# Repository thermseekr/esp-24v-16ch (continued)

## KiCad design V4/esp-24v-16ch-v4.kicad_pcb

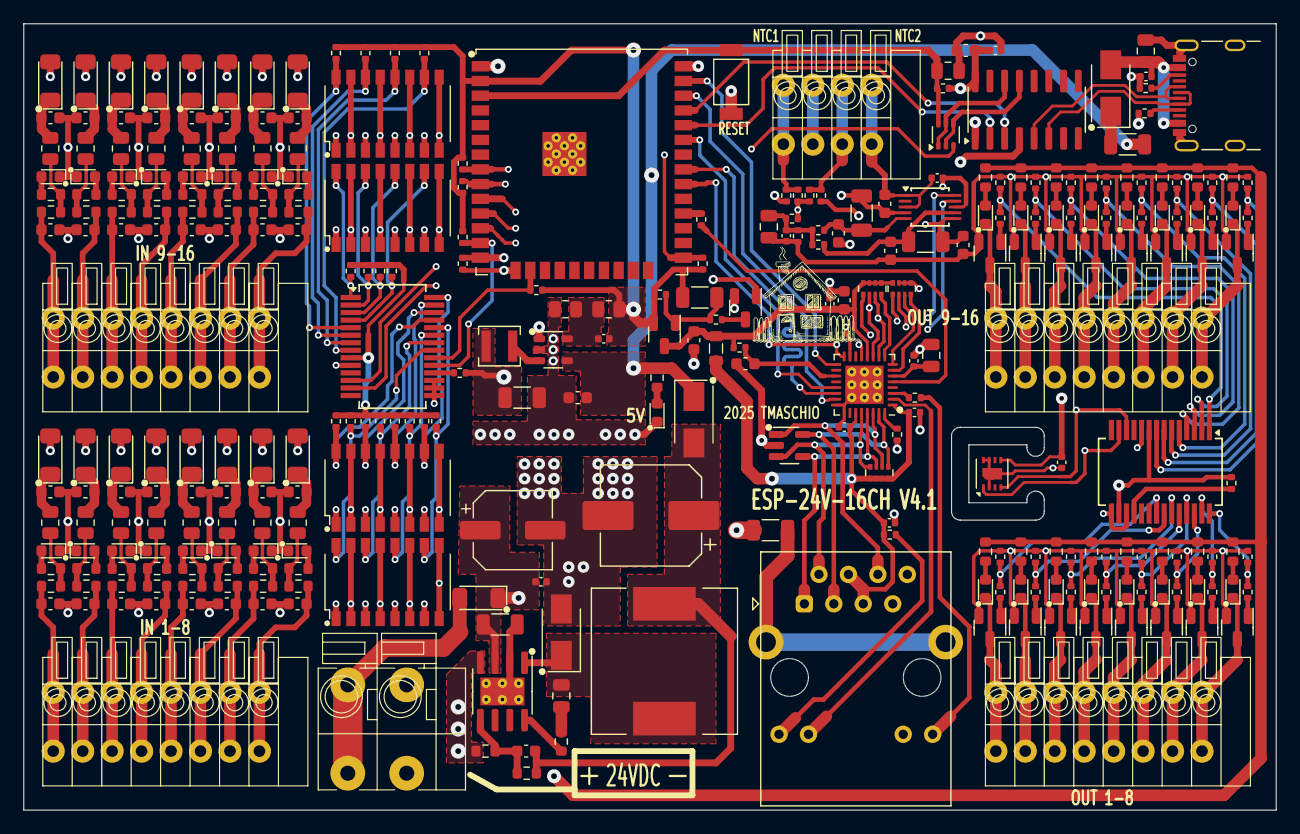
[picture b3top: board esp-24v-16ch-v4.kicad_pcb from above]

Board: 4 copper layers, 108.0 x 67.8 mm, 314 parts (0 on the bottom side), 230 nets.

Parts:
C1, C11, C13, C18, C19: 10uF/10V; C_0603_1608Metric
C2: 47uF/35V; CP_Elec_6.3x5.4
C3, C6, C14, C17, C20, C21, C22, C25, C26, C60: 100nF/50V; C_0402_1005Metric
C4: 22pF/50V; C_0402_1005Metric
C5, C15, C23, C59: 1uF/50V; C_0805_2012Metric
C7, C8: 22uF/10V; C_1206_3216Metric
C9: 100nF/100V; C_0805_2012Metric
C10: 12pF/50V; C_0603_1608Metric
C12: 470uF/16V; CP_Elec_8x10.5
C16: 1nF/2kV; C_1206_3216Metric
C24: 470pF/50V; C_0402_1005Metric
C27, C29, C31, C33, C35, C37, C39, C41, C43, C45, C47, C49, C51, C53, C55, C57: 1nF/50V; C_0603_1608Metric
C28, C30, C32, C34, C36, C38, C40, C42, C44, C46, C48, C50, C52, C54, C56, C58: 33nF/50V; C_0603_1608Metric
C61, C64: 4.7uF/50V; C_1206_3216Metric
C62, C63, C65, C66: 470nF/25V; C_0603_1608Metric
D1, D7, D9, D12, D15, D18, D21, D24, D27, D30, D33, D36, D39, D42, D45, D48, D51, D54, D56, D57, D58, D59, D60, D61, D62, D63, D64, D65, D66, D67, D68, D69, D70: WHITE/0603; LED_0603_1608Metric
D2: SM4007PL; D_SOD-123
D3, D5: SS34; D_SMA
D4: SS510; D_SMA
D6: ESDS314DBV; SOT-23-5
D10, D13, D16, D19, D22, D25, D28, D31, D34, D37, D40, D43, D46, D49, D52, D55: 9V1/500mW; D_SOD-123
F1: 33V/500mA; R_1206_3216Metric
FB1, FB2, FB3, FB4, FB5, FB6, FB7, FB8, FB9, FB10, FB11, FB12, FB13, FB14, FB15, FB16: 600R/100MHz; R_0603_1608Metric
J1, J2, J3, J4: DB141V-2.54-8P; TerminalBlock_Dibo_DB141V-2.54-8P_1x08_P2.54mm_Vertical
J5: VIN; TerminalBlock_Dibo_DB142V-5.08-2P_1x02_P5.08mm_Vertical
J6: USB_C_Receptacle_USB2.0; USB_C_Receptacle_GCT_USB4105-xx-A_16P_TopMnt_Horizontal
J7: ETHERNET; RJ45_HanRun_HR911105A
J8: NTC; TerminalBlock_Dibo_DB141V-2.54-4P_1x04_P2.54mm_Vertical
L1: 2,2uH 1,5A; L_3x3mm_h1.5mm
L2: 33uH 2,1A; L_12x12mm_h6mm
L3: 2A 600R; L_0805_2012Metric
Q1: WPM2015-3/TR; SOT-23
Q2: MMUN2211LT3G; SOT-23
Q3: UMH3N; SOT-363_SC-70-6
Q4, Q5, Q6, Q7, Q8, Q9, Q10, Q11, Q12, Q13, Q14, Q15, Q16, Q17, Q18, Q19: MMBT2222A; SOT-23-Narrow
R1: 560R/100mW; R_0603_1608Metric
R2, R3: 5,1k/62,5mW; R_0402_1005Metric
R4: 100k/125mW; R_0805_2012Metric
R5: 22,1k/125mW; R_0805_2012Metric
R6: 30mR/333mW; R_1206_3216Metric
R7: 5,1R/100mW; R_0603_1608Metric
R8, R12, R14, R19, R22, R26, R77, R80, R83, R86, R89, R92, R95, R98, R101, R104, R107, R110, R113, R116, R119, R122, R123, R124, R125: 10k/62,5mW; R_0402_1005Metric
R9, R24, R25, R27, R78, R81, R84, R87, R90, R93, R96, R99, R102, R105, R108, R111, R114, R117, R120: 1k/62,5mW; R_0402_1005Metric
R10: 300k/100mW; R_0603_1608Metric
R11: 52,3k/100mW; R_0603_1608Metric
R13: 22R/62,5mW; R_0402_1005Metric
R15, R16, R17, R18, R31, R34, R37, R40, R43, R46, R49, R52, R55, R58, R61, R64, R67, R70, R73, R76: 2k2/62,5mW; R_0402_1005Metric
R20, R21: 330R/62,5mW; R_0402_1005Metric
R23: 12,1k/62,5mW; R_0402_1005Metric
R28, R29, R32, R35, R38, R41, R44, R47, R50, R53, R56, R59, R62, R65, R68, R71, R74, R79, R82, R85, R88, R91, R94, R97, R100, R103, R106, R109, R112, R115, R118, R121: 6,8k/100mW; R_0603_1608Metric
R30, R33, R36, R39, R42, R45, R48, R51, R54, R57, R60, R63, R66, R69, R72, R75: 1k8/125mW; R_0805_2012Metric
R128, R129, R130, R131: 680R/62,5mW; R_0402_1005Metric
RN1, RN2: 4x2,2k/62,5mW; R_Array_Convex_4x0402
RN3: 4x49,9R/62,5mW; R_Array_Convex_4x0402
Ref**: Val**; Grandmas_small_silk
SW1: RESET; SW_SPST_Xunpu_TS1088AR02016
U1: SY8089A1AAC; SOT-23-5_Shorter_Pins
U2: TX4138; SOIC-8-1EP_3.9x4.9mm_P1.27mm_EP2.41x3.81mm_ThermalVias
U3: CH340C; SOIC-16_3.9x9.9mm_P1.27mm
U4: ESP32-WROOM-32UE-N16; ESP32-WROOM-32U
U5: LAN8710A; QFN-32-1EP_5x5mm_P0.5mm_EP3.3x3.3mm_ThermalVias
U6, U8: MCP23017_SS; SSOP-28_5.3x10.2mm_P0.65mm
U7: ADS1115IDGS; TSSOP-10_3x3mm_P0.5mm
U9: SHT31-DIS; Sensirion_DFN-8-1EP_2.5x2.5mm_P0.5mm_EP1.1x1.7mm
U10, U11, U12, U13: OR-3H7-4; SOP-16_4.4x10.4mm_P1.27mm

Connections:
+3.3V: C4.1, C7.1, C8.1, C13.1, C14.1, C26.1, L1.2, Q1.2 (S), R4.1, R8.1, R12.1, R14.1, R15.1, R16.1, R17.1, R18.1, R24.1, R25.1, R31.1, R34.1, R37.1, R40.1, R43.1, R46.1, R49.1, R52.1, R55.1, R58.1, R61.1, R64.1, R67.1, R70.1, R73.1, R76.1, U3.4 (V3), U3.16 (VCC), U4.2 (VDD), U6.9 (VDD), U8.9 (VDD), U8.16 (A1), U9.5 (VDD)
+3.3VA: C17.1, C21.1, C22.1, J7.4, J7.5, L3.2, R20.1, RN3.5 (R4.2), RN3.6 (R3.2), RN3.7 (R2.2), RN3.8 (R1.2), U5.1 (VDD2A), U5.27 (VDD1A)
+3.3VLAN: C11.1, C18.1, C20.1, L3.1, Q1.3 (D), R22.2, RN1.5 (R4.2), RN1.6 (R3.2), RN1.7 (R2.2), RN1.8 (R1.2), RN2.8 (R1.2), U5.12 (VDDIO)
+5V: C1.1, C25.1, D5.1 (K), F1.1, R1.1, R122.2, R123.2, R124.2, U1.1 (EN), U1.4 (IN), U7.8 (VDD)
+24V: C2.1, C3.1, D2.1 (K), R6.1, R28.1, R79.1, R82.1, R85.1, R88.1, R91.1, R94.1, R97.1, R100.1, R103.1, R106.1, R109.1, R112.1, R115.1, R118.1, R121.1, U2.3 (VIN)
/I2C Devices/AIN0N: C61.2, C63.1, R129.1, U7.5 (AIN1)
/I2C Devices/AIN0P: C61.1, C62.1, R128.1, U7.4 (AIN0)
/I2C Devices/AIN2N: C64.2, C66.1, R131.1, U7.7 (AIN3)
/I2C Devices/AIN2P: C64.1, C65.1, R130.1, U7.6 (AIN2)
/I2C Devices/MCP1-INTA: R16.2, U4.16 (IO13), U6.20 (INTA)
/I2C Devices/MCP1-INTB: R18.2, U4.13 (IO14), U6.19 (INTB)
/I2C Devices/NTC1: J8.1, R122.1, R128.2
/I2C Devices/NTC2: J8.3, R123.1, R130.2
/I2C Devices/VREF: C59.1, C60.1, R124.1, R125.2, R129.2, R131.2
/I2C Devices//MCP_IN_RST: R24.2, U6.18 (~RESET)
/I2C Devices//MCP_OUT_RST: R25.2, U8.18 (~RESET)
/IN1: C27.1, FB1.1, J1.1
/IN2: C29.1, FB2.1, J1.2
/IN3: C31.1, FB3.1, J1.3
/IN4: C33.1, FB4.1, J1.4
/IN5: C35.1, FB5.1, J1.5
/IN6: C37.1, FB6.1, J1.6
/IN7: C39.1, FB7.1, J1.7
/IN8: C41.1, FB8.1, J1.8
/IN9: C43.1, FB9.1, J2.1
/IN10: C45.1, FB10.1, J2.2
/IN11: C47.1, FB11.1, J2.3
/IN12: C49.1, FB12.1, J2.4
/IN13: C51.1, FB13.1, J2.5
/IN14: C53.1, FB14.1, J2.6
/IN15: C55.1, FB15.1, J2.7
/IN16: C57.1, FB16.1, J2.8
/INPUT1: R31.2, U6.21 (GPA0), U10.16
/INPUT2: R34.2, U6.22 (GPA1), U10.14
/INPUT3: R37.2, U6.23 (GPA2), U10.12
/INPUT4: R40.2, U6.24 (GPA3), U10.10
/INPUT5: R43.2, U6.25 (GPA4), U11.16
/INPUT6: R46.2, U6.26 (GPA5), U11.14
/INPUT7: R49.2, U6.27 (GPA6), U11.12
/INPUT8: R52.2, U6.28 (GPA7), U11.10
/INPUT9: R55.2, U6.1 (GPB0), U12.16
/INPUT10: R58.2, U6.2 (GPB1), U12.14
/INPUT11: R61.2, U6.3 (GPB2), U12.12
/INPUT12: R64.2, U6.4 (GPB3), U12.10
/INPUT13: R67.2, U6.5 (GPB4), U13.16
/INPUT14: R70.2, U6.6 (GPB5), U13.14
/INPUT15: R73.2, U6.7 (GPB6), U13.12
/INPUT16: R76.2, U6.8 (GPB7), U13.10
/LAN/EMAC_CLK: R13.2, U5.5 (XTAL1/CLKIN)
/LAN/EMAC_MDC: U4.37 (IO23), U5.17 (MDC)
/LAN/EMAC_MDIO: RN1.1 (R1.1), U4.30 (IO18), U5.16 (MDIO)
/LAN/EMAC_RX: RN2.1 (R1.1), U4.12 (IO27), U5.15 (COL/CRS_DV/~MODE2)
/LAN/EMAC_RXD0: RN1.2 (R2.1), U4.10 (IO25), U5.11 (RXD0/~MODE0)
/LAN/EMAC_RXD1: RN1.3 (R3.1), U4.11 (IO26), U5.10 (RXD1/~MODE1)
/LAN/EMAC_TXD0: U4.31 (IO19), U5.22 (TXD0)
/LAN/EMAC_TXD1: U4.36 (IO22), U5.23 (TXD1)
/LAN/EMAC_TXEN: U4.33 (IO21), U5.21 (TXEN)
/LAN/LED_G_K: J7.10, U5.2 (LED2/~INTSEL)
/LAN/LED_Y_A: R21.1, U5.3 (LED1/~REGOFF)
/LAN/RD+: D6.5 (I/04), J7.3 (RD+), RN3.1 (R1.1), U5.31 (RXP)
/LAN/RD-: D6.1 (I/01), J7.6 (RD-), RN3.2 (R2.1), U5.30 (RXN)
/LAN/TD+: D6.4 (I/03), J7.1 (TD+), RN3.3 (R3.1), U5.29 (TXP)
/LAN/TD-: D6.3 (I/02), J7.2 (TD-), RN3.4 (R4.1), U5.28 (TXN)
/LAN//PHY_RST: C19.1, R22.1, U5.19 (~RST)
/MCU/ESP_EN: C15.1, Q3.6 (C1), R12.2, SW1.2, U4.3 (EN)
/MCU/I2C_SCL: R15.2, U4.8 (IO32), U6.12 (SCK), U7.10 (SCL), U8.12 (SCK), U9.4 (SCL)
/MCU/I2C_SDA: R17.2, U4.9 (IO33), U6.13 (SDA), U7.9 (SDA), U8.13 (SDA), U9.1 (SDA)
/MCU/PHY_PWR: Q2.1 (B), R19.1, U4.14 (IO12)
/MCU/PROG: Q3.3 (C2), R14.2, U4.25 (IO0)
/MCU/RXD: U3.3 (RXD), U4.35 (TXD0/IO1)
/MCU/TXD: U3.2 (TXD), U4.34 (RXD0/IO3)
/MCU/USB_D+: J6.A6 (D+), J6.B6 (D+), U3.5 (UD+)
/MCU/USB_D-: J6.A7 (D-), J6.B7 (D-), U3.6 (UD-)
/MCU//DTR: Q3.2 (B1), Q3.4 (E2), U3.13 (~DTR)
/MCU//RTS: Q3.1 (E1), Q3.5 (B2), U3.14 (~RTS)
/OUT1: D7.1 (K), J3.1, Q4.3 (C)
/OUT2: D56.1 (K), J3.2, Q5.3 (C)
/OUT3: D57.1 (K), J3.3, Q6.3 (C)
/OUT4: D58.1 (K), J3.4, Q7.3 (C)
/OUT5: D59.1 (K), J3.5, Q8.3 (C)
/OUT6: D60.1 (K), J3.6, Q9.3 (C)
/OUT7: D61.1 (K), J3.7, Q10.3 (C)
/OUT8: D62.1 (K), J3.8, Q11.3 (C)
/OUT9: D63.1 (K), J4.1, Q12.3 (C)
/OUT10: D64.1 (K), J4.2, Q13.3 (C)
/OUT11: D65.1 (K), J4.3, Q14.3 (C)
/OUT12: D66.1 (K), J4.4, Q15.3 (C)
/OUT13: D67.1 (K), J4.5, Q16.3 (C)
/OUT14: D68.1 (K), J4.6, Q17.3 (C)
/OUT15: D69.1 (K), J4.7, Q18.3 (C)
/OUT16: D70.1 (K), J4.8, Q19.3 (C)
/OUTPUT1: R26.2, R27.2, U8.21 (GPA0)
/OUTPUT2: R77.2, R78.2, U8.22 (GPA1)
/OUTPUT3: R80.2, R81.2, U8.23 (GPA2)
/OUTPUT4: R83.2, R84.2, U8.24 (GPA3)
/OUTPUT5: R86.2, R87.2, U8.25 (GPA4)
/OUTPUT6: R89.2, R90.2, U8.26 (GPA5)
/OUTPUT7: R92.2, R93.2, U8.27 (GPA6)
/OUTPUT8: R95.2, R96.2, U8.28 (GPA7)
/OUTPUT9: R98.2, R99.2, U8.1 (GPB0)
/OUTPUT10: R101.2, R102.2, U8.2 (GPB1)
/OUTPUT11: R104.2, R105.2, U8.3 (GPB2)
/OUTPUT12: R107.2, R108.2, U8.4 (GPB3)
/OUTPUT13: R110.2, R111.2, U8.5 (GPB4)
/OUTPUT14: R113.2, R114.2, U8.6 (GPB5)
/OUTPUT15: R116.2, R117.2, U8.7 (GPB6)
/OUTPUT16: R119.2, R120.2, U8.8 (GPB7)
/Power/3.3V_REF: C4.2, R4.2, R5.1, U1.5 (FB)
/Power/5V_MAIN: C10.1, C12.1, D5.2 (A), L2.2, R10.1
/Power/5V_USB: C5.1, C6.1, D3.2 (A), J6.A4 (VBUS), J6.A9 (VBUS), J6.B4 (VBUS), J6.B9 (VBUS)
/Power/24VIN: D2.2 (A), J5.1
/Power/USB_A5: J6.A5 (CC1), R2.1
/Power/USB_B5: J6.B5 (CC2), R3.1
GND: C1.2, C2.2, C3.2, C5.2, C6.2, C7.2, C11.2, C12.2, C13.2, C14.2, C15.2, C16.2, C17.2, C18.2, C19.2, C20.2, C21.2, C22.2, C23.2, C24.2, C25.2, C26.2, C27.2, C28.2, C29.2, C30.2, C31.2, C32.2, C33.2, C34.2, C35.2, C36.2, C37.2, C38.2, C39.2, C40.2, C41.2, C42.2, C43.2, C44.2, C45.2, C46.2, C47.2, C48.2, C49.2, C50.2, C51.2, C52.2, C53.2, C54.2, C55.2, C56.2, C57.2, C58.2, C59.2, C60.2, C62.2, C63.2, C65.2, C66.2, D1.1 (K), D4.2 (A), D6.2 (GND), D9.1 (K), D12.1 (K), D15.1 (K), D18.1 (K), D21.1 (K), D24.1 (K), D27.1 (K), D30.1 (K), D33.1 (K), D36.1 (K), D39.1 (K), D42.1 (K), D45.1 (K), D48.1 (K), D51.1 (K), D54.1 (K), J5.2, J6.A1 (GND), J6.A12 (GND), J6.B1 (GND), J6.B12 (GND), J6.S1 (SHIELD), J7.8, J7.11, J8.2, J8.4, Q2.2 (E), Q4.2 (E), Q5.2 (E), Q6.2 (E), Q7.2 (E), Q8.2 (E), Q9.2 (E), Q10.2 (E), Q11.2 (E), Q12.2 (E), Q13.2 (E), Q14.2 (E), Q15.2 (E), Q16.2 (E), Q17.2 (E), Q18.2 (E), Q19.2 (E), R2.2, R3.2, R5.2, R11.2, R19.2, R23.2, R26.1, R77.1, R80.1, R83.1, R86.1, R89.1, R92.1, R95.1, R98.1, R101.1, R104.1, R107.1, R110.1, R113.1, R116.1, R119.1, R125.1, RN2.5 (R4.2), RN2.6 (R3.2), RN2.7 (R2.2), SW1.1, U1.2 (GND), U2.4 (GND), U3.1 (GND), U4.1 (GND), U4.15 (GND), U4.38 (GND), U4.39 (GND), U5.24 (TXD2), U5.25 (TXD3), U5.33 (VSS), U6.10 (VSS), U6.15 (A0), U6.16 (A1), U6.17 (A2), U7.1 (ADDR), U7.3 (GND), U8.10 (VSS), U8.15 (A0), U8.17 (A2), U9.2 (ADDR), U9.7 (R), U9.8 (VSS), U9.9 (VSS), U10.2, U10.4, U10.6, U10.8, U10.9, U10.11, U10.13, U10.15, U11.2, U11.4, U11.6, U11.8, U11.9, U11.11, U11.13, U11.15, U12.2, U12.4, U12.6, U12.8, U12.9, U12.11, U12.13, U12.15, U13.2, U13.4, U13.6, U13.8, U13.9, U13.11, U13.13, U13.15
unnamed: C9.1, R7.1
unnamed: C16.1, J7.SH
unnamed: D1.2 (A), R1.2
unnamed: D3.1 (K), F1.2
unnamed: C9.2, D4.1 (K), L2.1, U2.1 (SW)
unnamed: D7.2 (A), R28.2
unnamed: D9.2 (A), R29.2
unnamed: D10.2 (A), U10.1
unnamed: C28.1, D10.1 (K), R30.1
unnamed: D12.2 (A), R32.2
unnamed: D13.2 (A), U10.3
unnamed: C30.1, D13.1 (K), R33.1
unnamed: D15.2 (A), R35.2
unnamed: D16.2 (A), U10.5
unnamed: C32.1, D16.1 (K), R36.1
unnamed: D18.2 (A), R38.2
unnamed: D19.2 (A), U10.7
unnamed: C34.1, D19.1 (K), R39.1
unnamed: D21.2 (A), R41.2
unnamed: D22.2 (A), U11.1
unnamed: C36.1, D22.1 (K), R42.1
unnamed: D24.2 (A), R44.2
unnamed: D25.2 (A), U11.3
unnamed: C38.1, D25.1 (K), R45.1
unnamed: D27.2 (A), R47.2
unnamed: D28.2 (A), U11.5
unnamed: C40.1, D28.1 (K), R48.1
unnamed: D30.2 (A), R50.2
unnamed: D31.2 (A), U11.7
unnamed: C42.1, D31.1 (K), R51.1
unnamed: D33.2 (A), R53.2
unnamed: D34.2 (A), U12.1
unnamed: C44.1, D34.1 (K), R54.1
unnamed: D36.2 (A), R56.2
unnamed: D37.2 (A), U12.3
unnamed: C46.1, D37.1 (K), R57.1
unnamed: D39.2 (A), R59.2
unnamed: D40.2 (A), U12.5
unnamed: C48.1, D40.1 (K), R60.1
unnamed: D42.2 (A), R62.2
unnamed: D43.2 (A), U12.7
unnamed: C50.1, D43.1 (K), R63.1
unnamed: D45.2 (A), R65.2
unnamed: D46.2 (A), U13.1
unnamed: C52.1, D46.1 (K), R66.1
unnamed: D48.2 (A), R68.2
unnamed: D49.2 (A), U13.3
unnamed: C54.1, D49.1 (K), R69.1
unnamed: D51.2 (A), R71.2
unnamed: D52.2 (A), U13.5
unnamed: C56.1, D52.1 (K), R72.1
unnamed: D54.2 (A), R74.2
unnamed: D55.2 (A), U13.7
unnamed: C58.1, D55.1 (K), R75.1
unnamed: D56.2 (A), R79.2
unnamed: D57.2 (A), R82.2
unnamed: D58.2 (A), R85.2
unnamed: D59.2 (A), R88.2
unnamed: D60.2 (A), R91.2
unnamed: D61.2 (A), R94.2
unnamed: D62.2 (A), R97.2
unnamed: D63.2 (A), R100.2
unnamed: D64.2 (A), R103.2
unnamed: D65.2 (A), R106.2
unnamed: D66.2 (A), R109.2
unnamed: D67.2 (A), R112.2
unnamed: D68.2 (A), R115.2
unnamed: D69.2 (A), R118.2
unnamed: D70.2 (A), R121.2
unnamed: FB1.2, R29.1, R30.2
unnamed: FB2.2, R32.1, R33.2
unnamed: FB3.2, R35.1, R36.2
unnamed: FB4.2, R38.1, R39.2
unnamed: FB5.2, R41.1, R42.2
unnamed: FB6.2, R44.1, R45.2
unnamed: FB7.2, R47.1, R48.2
unnamed: FB8.2, R50.1, R51.2
unnamed: FB9.2, R53.1, R54.2
unnamed: FB10.2, R56.1, R57.2
unnamed: FB11.2, R59.1, R60.2
unnamed: FB12.2, R62.1, R63.2
unnamed: FB13.2, R65.1, R66.2
unnamed: FB14.2, R68.1, R69.2
unnamed: FB15.2, R71.1, R72.2
unnamed: FB16.2, R74.1, R75.2
unnamed: J7.9, R20.2
unnamed: J7.12, R21.2
unnamed: C8.2, Q1.1 (G), R8.2, R9.2
unnamed: Q2.3 (C), R9.1
unnamed: Q4.1 (B), R27.1
unnamed: Q5.1 (B), R78.1
unnamed: Q6.1 (B), R81.1
unnamed: Q7.1 (B), R84.1
unnamed: Q8.1 (B), R87.1
unnamed: Q9.1 (B), R90.1
unnamed: Q10.1 (B), R93.1
unnamed: Q11.1 (B), R96.1
unnamed: Q12.1 (B), R99.1
unnamed: Q13.1 (B), R102.1
unnamed: Q14.1 (B), R105.1
unnamed: Q15.1 (B), R108.1
unnamed: Q16.1 (B), R111.1
unnamed: Q17.1 (B), R114.1
unnamed: Q18.1 (B), R117.1
unnamed: Q19.1 (B), R120.1
unnamed: R6.2, U2.2 (ILIM), U2.9 (ILIM)
unnamed: RN1.4 (R4.1), U5.9 (RXD2/~RMIISEL)
unnamed: RN2.2 (R2.1), U5.13 (RXER/RXD4/~PHYAD0)
unnamed: RN2.3 (R3.1), U5.8 (RXD3/~PHYAD2)
unnamed: RN2.4 (R4.1), U5.7 (RXCLK/~PHYAD1)
unnamed: L1.1, U1.3 (LX)
unnamed: R7.2, U2.8 (BS)
unnamed: C10.2, R10.2, R11.1, U2.5 (FB)
unnamed: R13.1, U4.28 (IO17)
unnamed: R23.1, U5.32 (RBIAS)
unnamed: C23.1, C24.1, U5.6 (VDDCR)

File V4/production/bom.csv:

Designator,Footprint,Quantity,Value,LCSC Part #
"C1, C11, C13, C18, C19",0603,5,10uF/10V,C19702
C10,0603,1,12pF/50V,C38523
C12,CP_Elec_8x10.5,1,470uF/16V,C96179
"C14, C17, C20, C21, C22, C25, C3, C6, C60",0402,9,100nF/50V,C307331
"C15, C23, C5, C59",0805,4,1uF/50V,C28323
C16,1206,1,1nF/2kV,C161353
C2,CP_Elec_6.3x5.4,1,47uF/35V,C129415
C24,0402,1,470pF/50V,C1537
"C27, C29, C31, C33, C35, C37, C39, C41",0603,8,1nF/50V,C1588
"C28, C30, C32, C34, C36, C38, C40, C42",0603,8,33nF/50V,C21117
C4,0402,1,22pF/50V,C1555
"C61, C64",1206,2,4.7uF/50V,C29823
"C62, C63, C65, C66",0603,4,470nF/25V,C1623
"C7, C8",1206,2,22uF/10V,C5672
C9,0805,1,100nF/100V,C28233
"D1, D12, D15, D18, D21, D24, D27, D30, D56, D57, D58, D59, D60, D61, D62, D7, D9",0603,17,WHITE/0603,C2290
"D10, D13, D16, D19, D22, D25, D28, D31",D_SOD-123,8,9V1/500mW,C19077407
D2,D_SOD-123,1,SM4007PL,C64898
"D3, D5",D_SMA,2,SS34,C8678
D4,D_SMA,1,SS510,C65010
D6,SOT-23-5,1,ESDS314DBV,C1847859
F1,1206,1,33V/500mA,C70077
"FB1, FB2, FB3, FB4, FB5, FB6, FB7, FB8",0603,8,600R/100MHz,C85833
"J1, J3",TerminalBlock_Dibo_DB141V-2.54-8P_1x08_P2.54mm_Vertical,2,DB141V-2.54-8P,C2898750
J5,TerminalBlock_Dibo_DB142V-5.08-2P_1x02_P5.08mm_Vertical,1,VIN,C2898699
J6,USB_C_Receptacle_GCT_USB4105-xx-A_16P_TopMnt_Horizontal,1,USB_C_Receptacle_USB2.0,C2765186
J7,RJ45_HanRun_HR911105A,1,ETHERNET,C12074
J8,TerminalBlock_Dibo_DB141V-2.54-4P_1x04_P2.54mm_Vertical,1,NTC,C2898746
L1,L_3x3mm_h1.5mm,1,"2,2uH 1,5A",C370424
L2,L_12x12mm_h6mm,1,"33uH 2,1A",C169386
L3,0805,1,2A 600R,C139168
Q1,SOT-23,1,WPM2015-3/TR,C558305
"Q10, Q11, Q4, Q5, Q6, Q7, Q8, Q9",SOT-23-Narrow,8,MMBT2222A,C8512
Q2,SOT-23,1,MMUN2211LT3G,C150229
Q3,SOT-363_SC-70-6,1,UMH3N,C62892
R1,0603,1,560R/100mW,C23204
R10,0603,1,300k/100mW,C23024
R11,0603,1,"52,3k/100mW",C185323
"R12, R122, R123, R124, R125, R14, R19, R22, R26, R77, R8, R80, R83, R86, R89, R92, R95",0402,17,"10k/62,5mW",C25744
"R128, R129, R130, R131",0402,4,"680R/62,5mW",C25130
R13,0402,1,"22R/62,5mW",C25092
"R15, R16, R17, R18, R31, R34, R37, R40, R43, R46, R49, R52",0402,12,"2k2/62,5mW",C25879
"R2, R3",0402,2,"5,1k/62,5mW",C105872
"R20, R21",0402,2,"330R/62,5mW",C25104
R23,0402,1,"12,1k/62,5mW",C25852
"R24, R25, R27, R78, R81, R84, R87, R9, R90, R93, R96",0402,11,"1k/62,5mW",C11702
"R28, R29, R32, R35, R38, R41, R44, R47, R50, R79, R82, R85, R88, R91, R94, R97",0603,16,"6,8k/100mW",C23212
"R30, R33, R36, R39, R42, R45, R48, R51",0805,8,1k8/125mW,C17398
R4,0805,1,100k/125mW,C149504
R5,0805,1,"22,1k/125mW",C17552
R6,1206,1,30mR/333mW,C473665
R7,0603,1,"5,1R/100mW",C25197
"RN1, RN2",R_Array_Convex_4x0402,2,"4x2,2k/62,5mW",C728724
RN3,R_Array_Convex_4x0402,1,"4x49,9R/62,5mW",C136850
SW1,SW_SPST_Xunpu_TS1088AR02016,1,RESET,C720477
U1,SOT-23-5_Shorter_Pins,1,SY8089A1AAC,C479074
"U10, U11",SOP-16_4.4x10.4mm_P1.27mm,2,OR-3H7-4,C2838427
U2,SOIC-8-1EP_3.9x4.9mm_P1.27mm_EP2.41x3.81mm_ThermalVias,1,TX4138,C329267
U3,SOIC-16_3.9x9.9mm_P1.27mm,1,CH340C,C84681
U4,ESP32-WROOM-32U,1,ESP32-WROOM-32UE-N16,C701346
U5,QFN-32-1EP_5x5mm_P0.5mm_EP3.3x3.3mm_ThermalVias,1,LAN8710A,C46185
"U6, U8",SSOP-28_5.3x10.2mm_P0.65mm,2,MCP23017_SS,C558584
U7,TSSOP-10_3x3mm_P0.5mm,1,ADS1115IDGS,C37593

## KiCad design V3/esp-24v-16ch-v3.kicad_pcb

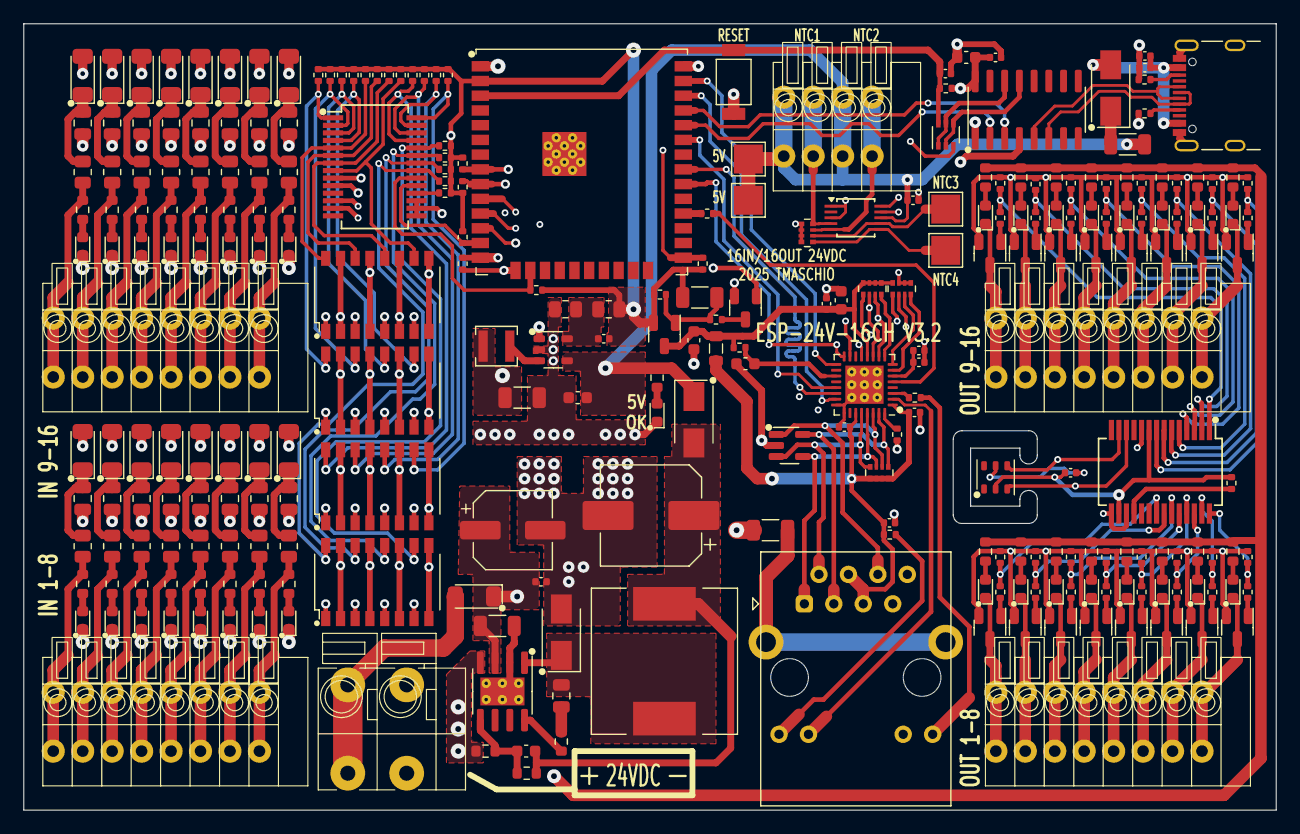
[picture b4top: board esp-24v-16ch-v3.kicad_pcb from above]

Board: 4 copper layers, 108.0 x 67.8 mm, 270 parts (0 on the bottom side), 211 nets.

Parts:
C1, C9, C11, C16, C17: 10uF/10V; C_0603_1608Metric
C2: 47uF/35V; CP_Elec_6.3x5.4
C3: 22pF/50V; C_0402_1005Metric
C4, C12, C15, C18, C19, C20, C40, C41, C42: 100nF/50V; C_0402_1005Metric
C5, C6: 22uF/10V; C_1206_3216Metric
C7: 100nF/100V; C_0805_2012Metric
C8: 12pF/50V; C_0603_1608Metric
C10: 470uF/16V; CP_Elec_8x10.5
C13, C21, C39: 1uF/25V; C_0402_1005Metric
C14: 1nF/2kV; C_1206_3216Metric
C22: 470pF/50V; C_0402_1005Metric
C23, C24, C25, C26, C27, C28, C29, C30, C31, C32, C33, C34, C35, C36, C37, C38: 33nF/50V; C_0805_2012Metric
D1: SM4007PL; D_SOD-123
D2, D7, D8, D9, D10, D15, D16, D17, D18, D23, D24, D25, D26, D31, D32, D33, D34, D39, D40, D41, D42, D43, D44, D45, D46, D47, D48, D49, D50, D51, D52, D53, D54: EMERALD/0603; LED_0603_1608Metric
D3, D5: SS34; D_SMA
D4: SS510; D_SMA
D6: ESDS314DBV; SOT-23-5
D11, D12, D13, D14, D19, D20, D21, D22, D27, D28, D29, D30, D35, D36, D37, D38: 9V1/500mW; D_SOD-123
F1: 33V/500mA; R_1206_3216Metric
H1, H2: +5V; TestPoint_Pad_2.5x2.5mm
H3: AIN2; TestPoint_Pad_2.5x2.5mm
H4: AIN3; TestPoint_Pad_2.5x2.5mm
J1: VIN; TerminalBlock_Dibo_DB142V-5.08-2P_1x02_P5.08mm_Vertical
J2: USB_C_Receptacle_USB2.0; USB_C_Receptacle_GCT_USB4105-xx-A_16P_TopMnt_Horizontal
J3, J4, J5, J6: DB141V-2.54-8P; TerminalBlock_Dibo_DB141V-2.54-8P_1x08_P2.54mm_Vertical
J7: ETHERNET; RJ45_HanRun_HR911105A
J8: NTC; TerminalBlock_Dibo_DB141V-2.54-4P_1x04_P2.54mm_Vertical
L1: 2,2uH 1,5A; L_3x3mm_h1.5mm
L2: 33uH 2,1A; L_12x12mm_h6mm
L3: 2A 600R; L_0805_2012Metric
Q1: WPM2015-3/TR; SOT-23
Q2: MMUN2211LT3G; SOT-23
Q3: UMH3N; SOT-363_SC-70-6
Q4, Q5, Q6, Q7, Q8, Q9, Q10, Q11, Q12, Q13, Q14, Q15, Q16, Q17, Q18, Q19: MMBT2222A; SOT-23-Narrow
R1: 560R/100mW; R_0603_1608Metric
R2: 100k/125mW; R_0805_2012Metric
R3: 22,1k/125mW; R_0805_2012Metric
R4: 30mR/333mW; R_1206_3216Metric
R5: 5,1R/100mW; R_0603_1608Metric
R6, R10, R11, R12, R24, R81, R82, R83, R84, R93, R94, R95, R96, R105, R106, R107, R108, R117, R118, R119, R120: 10k/62,5mW; R_0402_1005Metric
R7, R31, R32, R85, R86, R87, R88, R97, R98, R99, R100, R109, R110, R111, R112, R121, R122, R123, R124: 1k/62,5mW; R_0402_1005Metric
R8: 300k/100mW; R_0603_1608Metric
R9: 52,3k/100mW; R_0603_1608Metric
R13, R14, R41, R42, R43, R44, R53, R54, R55, R56, R65, R66, R67, R68, R77, R78, R79, R80, R129, R130: 2k2/62,5mW; R_0402_1005Metric
R15: 22R/62,5mW; R_0402_1005Metric
R16, R17: 330R/62,5mW; R_0402_1005Metric
R26: 12,1k/62,5mW; R_0402_1005Metric
R33, R34, R35, R36, R45, R46, R47, R48, R57, R58, R59, R60, R69, R70, R71, R72, R89, R90, R91, R92, R101, R102, R103, R104, R113, R114, R115, R116, R125, R126, R127, R128: 6,8k/100mW; R_0603_1608Metric
R37, R38, R39, R40, R49, R50, R51, R52, R61, R62, R63, R64, R73, R74, R75, R76: 1k8/125mW; R_0805_2012Metric
R131, R132: 5,1k/62,5mW; R_0402_1005Metric
RN1: 4x49,9R/62,5mW; R_Array_Convex_4x0402
RN2, RN3: 4x2,2k/62,5mW; R_Array_Convex_4x0402
RN4: 4x3k/62,5mW; R_Array_Convex_4x0402
SW1: RESET; SW_SPST_Xunpu_TS1088AR02016
U1: SY8089A1AAC; SOT-23-5_Shorter_Pins
U2: TX4138; SOIC-8-1EP_3.9x4.9mm_P1.27mm_EP2.41x3.81mm_ThermalVias
U3: CH340C; SOIC-16_3.9x9.9mm_P1.27mm
U4: ESP32-WROOM-32UE-N16; ESP32-WROOM-32U
U5: LAN8710A; QFN-32-1EP_5x5mm_P0.5mm_EP3.3x3.3mm_ThermalVias
U6, U7: MCP23017_SS; SSOP-28_5.3x10.2mm_P0.65mm
U8, U9, U10, U11: OR-3H7-4; SOP-16_4.4x10.4mm_P1.27mm
U12: AHT20; DFN-6-3x3mm_P1mm
U13: ADS1115IDGS; TSSOP-10_3x3mm_P0.5mm

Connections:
+3.3V: C3.1, C5.1, C6.1, C11.1, C12.1, C41.1, L1.2, Q1.2 (S), R2.1, R6.1, R10.1, R11.1, R13.1, R14.1, R31.1, R32.1, R41.1, R42.1, R43.1, R44.1, R53.1, R54.1, R55.1, R56.1, R65.1, R66.1, R67.1, R68.1, R77.1, R78.1, R79.1, R80.1, R129.1, R130.1, U3.4 (V3), U3.16 (VCC), U4.2 (VDD), U6.9 (VDD), U7.9 (VDD), U7.16 (A1), U12.2 (VDD)
+3.3VA: C15.1, C19.1, C20.1, J7.4, J7.5, L3.2, R16.1, RN1.5 (R4.2), RN1.6 (R3.2), RN1.7 (R2.2), RN1.8 (R1.2), U5.1 (VDD2A), U5.27 (VDD1A)
+3.3VLAN: C9.1, C16.1, C18.1, L3.1, Q1.3 (D), R24.2, RN2.5 (R4.2), RN2.6 (R3.2), RN2.7 (R2.2), RN2.8 (R1.2), RN3.8 (R1.2), U5.12 (VDDIO)
+5V: C1.1, C42.1, D5.1 (K), F1.1, H1.1, H2.1, J8.1, J8.3, R1.1, U1.1 (EN), U1.4 (IN), U13.8 (VDD)
+24V: C2.1, C4.1, D1.1 (K), R4.1, R89.1, R90.1, R91.1, R92.1, R101.1, R102.1, R103.1, R104.1, R113.1, R114.1, R115.1, R116.1, R125.1, R126.1, R127.1, R128.1, U2.3 (VIN)
/I2C Devices/IN1: R41.2, U6.21 (GPA0), U8.16
/I2C Devices/IN2: R42.2, U6.22 (GPA1), U8.14
/I2C Devices/IN3: R43.2, U6.23 (GPA2), U8.12
/I2C Devices/IN4: R44.2, U6.24 (GPA3), U8.10
/I2C Devices/IN5: R53.2, U6.25 (GPA4), U9.16
/I2C Devices/IN6: R54.2, U6.26 (GPA5), U9.14
/I2C Devices/IN7: R55.2, U6.27 (GPA6), U9.12
/I2C Devices/IN8: R56.2, U6.28 (GPA7), U9.10
/I2C Devices/IN9: R65.2, U6.1 (GPB0), U10.16
/I2C Devices/IN10: R66.2, U6.2 (GPB1), U10.14
/I2C Devices/IN11: R67.2, U6.3 (GPB2), U10.12
/I2C Devices/IN12: R68.2, U6.4 (GPB3), U10.10
/I2C Devices/IN13: R77.2, U6.5 (GPB4), U11.16
/I2C Devices/IN14: R78.2, U6.6 (GPB5), U11.14
/I2C Devices/IN15: R79.2, U6.7 (GPB6), U11.12
/I2C Devices/IN16: R80.2, U6.8 (GPB7), U11.10
/I2C Devices/MCP1-INTA: R129.2, U4.16 (IO13), U6.20 (INTA)
/I2C Devices/MCP1-INTB: R130.2, U4.13 (IO14), U6.19 (INTB)
/I2C Devices/OUT1: R81.2, R85.2, U7.21 (GPA0)
/I2C Devices/OUT2: R82.2, R86.2, U7.22 (GPA1)
/I2C Devices/OUT3: R83.2, R87.2, U7.23 (GPA2)
/I2C Devices/OUT4: R84.2, R88.2, U7.24 (GPA3)
/I2C Devices/OUT5: R93.2, R97.2, U7.25 (GPA4)
/I2C Devices/OUT6: R94.2, R98.2, U7.26 (GPA5)
/I2C Devices/OUT7: R95.2, R99.2, U7.27 (GPA6)
/I2C Devices/OUT8: R96.2, R100.2, U7.28 (GPA7)
/I2C Devices/OUT9: R105.2, R109.2, U7.1 (GPB0)
/I2C Devices/OUT10: R106.2, R110.2, U7.2 (GPB1)
/I2C Devices/OUT11: R107.2, R111.2, U7.3 (GPB2)
/I2C Devices/OUT12: R108.2, R112.2, U7.4 (GPB3)
/I2C Devices/OUT13: R117.2, R121.2, U7.5 (GPB4)
/I2C Devices/OUT14: R118.2, R122.2, U7.6 (GPB5)
/I2C Devices/OUT15: R119.2, R123.2, U7.7 (GPB6)
/I2C Devices/OUT16: R120.2, R124.2, U7.8 (GPB7)
/Inputs 1-16/J4-IN1: J3.1, R33.1, R37.2
/Inputs 1-16/J4-IN2: J3.2, R34.1, R38.2
/Inputs 1-16/J4-IN3: J3.3, R35.1, R39.2
/Inputs 1-16/J4-IN4: J3.4, R36.1, R40.2
/Inputs 1-16/J4-IN5: J3.5, R45.1, R49.2
/Inputs 1-16/J4-IN6: J3.6, R46.1, R50.2
/Inputs 1-16/J4-IN7: J3.7, R47.1, R51.2
/Inputs 1-16/J4-IN8: J3.8, R48.1, R52.2
/Inputs 1-16/J5-IN9: J4.1, R57.1, R61.2
/Inputs 1-16/J5-IN10: J4.2, R58.1, R62.2
/Inputs 1-16/J5-IN11: J4.3, R59.1, R63.2
/Inputs 1-16/J5-IN12: J4.4, R60.1, R64.2
/Inputs 1-16/J5-IN13: J4.5, R69.1, R73.2
/Inputs 1-16/J5-IN14: J4.6, R70.1, R74.2
/Inputs 1-16/J5-IN15: J4.7, R71.1, R75.2
/Inputs 1-16/J5-IN16: J4.8, R72.1, R76.2
/LAN/EMAC_CLK: R15.2, U5.5 (XTAL1/CLKIN)
/LAN/EMAC_MDC: U4.37 (IO23), U5.17 (MDC)
/LAN/EMAC_MDIO: RN2.1 (R1.1), U4.30 (IO18), U5.16 (MDIO)
/LAN/EMAC_RX: RN3.1 (R1.1), U4.12 (IO27), U5.15 (COL/CRS_DV/~MODE2)
/LAN/EMAC_RXD0: RN2.2 (R2.1), U4.10 (IO25), U5.11 (RXD0/~MODE0)
/LAN/EMAC_RXD1: RN2.3 (R3.1), U4.11 (IO26), U5.10 (RXD1/~MODE1)
/LAN/EMAC_TXD0: U4.31 (IO19), U5.22 (TXD0)
/LAN/EMAC_TXD1: U4.36 (IO22), U5.23 (TXD1)
/LAN/EMAC_TXEN: U4.33 (IO21), U5.21 (TXEN)
/LAN/LED_G_K: J7.10, U5.2 (LED2/~INTSEL)
/LAN/LED_Y_A: R17.1, U5.3 (LED1/~REGOFF)
/LAN/RD+: D6.5 (I/04), J7.3 (RD+), RN1.1 (R1.1), U5.31 (RXP)
/LAN/RD-: D6.1 (I/01), J7.6 (RD-), RN1.2 (R2.1), U5.30 (RXN)
/LAN/TD+: D6.4 (I/03), J7.1 (TD+), RN1.3 (R3.1), U5.29 (TXP)
/LAN/TD-: D6.3 (I/02), J7.2 (TD-), RN1.4 (R4.1), U5.28 (TXN)
/MCU/I2C_SCL: R13.2, U4.8 (IO32), U6.12 (SCK), U7.12 (SCK), U12.3 (SCL), U13.10 (SCL)
/MCU/I2C_SDA: R14.2, U4.9 (IO33), U6.13 (SDA), U7.13 (SDA), U12.4 (SDA), U13.9 (SDA)
/MCU/PHY_PWR: Q2.1 (B), R12.1, U4.14 (IO12)
/MCU/USB_D+: J2.A6 (D+), J2.B6 (D+), U3.5 (UD+)
/MCU/USB_D-: J2.A7 (D-), J2.B7 (D-), U3.6 (UD-)
/Outputs 1-16/J8-OUT1: D39.1 (K), J5.1, Q4.3 (C)
/Outputs 1-16/J8-OUT2: D40.1 (K), J5.2, Q5.3 (C)
/Outputs 1-16/J8-OUT3: D41.1 (K), J5.3, Q6.3 (C)
/Outputs 1-16/J8-OUT4: D42.1 (K), J5.4, Q7.3 (C)
/Outputs 1-16/J8-OUT5: D43.1 (K), J5.5, Q8.3 (C)
/Outputs 1-16/J8-OUT6: D44.1 (K), J5.6, Q9.3 (C)
/Outputs 1-16/J8-OUT7: D45.1 (K), J5.7, Q10.3 (C)
/Outputs 1-16/J8-OUT8: D46.1 (K), J5.8, Q11.3 (C)
/Outputs 1-16/J9-OUT9: D47.1 (K), J6.1, Q12.3 (C)
/Outputs 1-16/J9-OUT10: D48.1 (K), J6.2, Q13.3 (C)
/Outputs 1-16/J9-OUT11: D49.1 (K), J6.3, Q14.3 (C)
/Outputs 1-16/J9-OUT12: D50.1 (K), J6.4, Q15.3 (C)
/Outputs 1-16/J9-OUT13: D51.1 (K), J6.5, Q16.3 (C)
/Outputs 1-16/J9-OUT14: D52.1 (K), J6.6, Q17.3 (C)
/Outputs 1-16/J9-OUT15: D53.1 (K), J6.7, Q18.3 (C)
/Outputs 1-16/J9-OUT16: D54.1 (K), J6.8, Q19.3 (C)
GND: C1.2, C2.2, C4.2, C5.2, C9.2, C10.2, C11.2, C12.2, C13.2, C14.2, C15.2, C16.2, C17.2, C18.2, C19.2, C20.2, C21.2, C22.2, C23.2, C24.2, C25.2, C26.2, C27.2, C28.2, C29.2, C30.2, C31.2, C32.2, C33.2, C34.2, C35.2, C36.2, C37.2, C38.2, C39.2, C40.2, C41.2, C42.2, D2.1 (K), D4.2 (A), D6.2 (GND), D7.1 (K), D8.1 (K), D9.1 (K), D10.1 (K), D15.1 (K), D16.1 (K), D17.1 (K), D18.1 (K), D23.1 (K), D24.1 (K), D25.1 (K), D26.1 (K), D31.1 (K), D32.1 (K), D33.1 (K), D34.1 (K), J1.2, J2.A1 (GND), J2.A12 (GND), J2.B1 (GND), J2.B12 (GND), J2.S1 (SHIELD), J7.8, J7.11, Q2.2 (E), Q4.2 (E), Q5.2 (E), Q6.2 (E), Q7.2 (E), Q8.2 (E), Q9.2 (E), Q10.2 (E), Q11.2 (E), Q12.2 (E), Q13.2 (E), Q14.2 (E), Q15.2 (E), Q16.2 (E), Q17.2 (E), Q18.2 (E), Q19.2 (E), R3.2, R9.2, R12.2, R26.2, R81.1, R82.1, R83.1, R84.1, R93.1, R94.1, R95.1, R96.1, R105.1, R106.1, R107.1, R108.1, R117.1, R118.1, R119.1, R120.1, R131.2, R132.2, RN3.5 (R4.2), RN3.6 (R3.2), RN3.7 (R2.2), RN4.1 (R1.1), RN4.2 (R2.1), RN4.3 (R3.1), RN4.4 (R4.1), SW1.1, U1.2 (GND), U2.4 (GND), U3.1 (GND), U4.1 (GND), U4.15 (GND), U4.38 (GND), U4.39 (GND), U5.24 (TXD2), U5.25 (TXD3), U5.33 (VSS), U6.10 (VSS), U6.15 (A0), U6.16 (A1), U6.17 (A2), U7.10 (VSS), U7.15 (A0), U7.17 (A2), U8.2, U8.4, U8.6, U8.8, U8.9, U8.11, U8.13, U8.15, U9.2, U9.4, U9.6, U9.8, U9.9, U9.11, U9.13, U9.15, U10.2, U10.4, U10.6, U10.8, U10.9, U10.11, U10.13, U10.15, U11.2, U11.4, U11.6, U11.8, U11.9, U11.11, U11.13, U11.15, U12.5 (GND), U13.1 (ADDR), U13.3 (GND)
unnamed: C7.1, R5.1
unnamed: C14.1, J7.SH
unnamed: D1.2 (A), J1.1
unnamed: D2.2 (A), R1.2
unnamed: C39.1, C40.1, D3.2 (A), J2.A4 (VBUS), J2.A9 (VBUS), J2.B4 (VBUS), J2.B9 (VBUS)
unnamed: D3.1 (K), F1.2
unnamed: C7.2, D4.1 (K), L2.1, U2.1 (SW)
unnamed: C8.1, C10.1, D5.2 (A), L2.2, R8.1
unnamed: D7.2 (A), R33.2
unnamed: D8.2 (A), R34.2
unnamed: D9.2 (A), R35.2
unnamed: D10.2 (A), R36.2
unnamed: D11.2 (A), U8.1
unnamed: C23.1, D11.1 (K), R37.1
unnamed: D12.2 (A), U8.3
unnamed: C24.1, D12.1 (K), R38.1
unnamed: D13.2 (A), U8.5
unnamed: C25.1, D13.1 (K), R39.1
unnamed: D14.2 (A), U8.7
unnamed: C26.1, D14.1 (K), R40.1
unnamed: D15.2 (A), R45.2
unnamed: D16.2 (A), R46.2
unnamed: D17.2 (A), R47.2
unnamed: D18.2 (A), R48.2
unnamed: D19.2 (A), U9.1
unnamed: C27.1, D19.1 (K), R49.1
unnamed: D20.2 (A), U9.3
unnamed: C28.1, D20.1 (K), R50.1
unnamed: D21.2 (A), U9.5
unnamed: C29.1, D21.1 (K), R51.1
unnamed: D22.2 (A), U9.7
unnamed: C30.1, D22.1 (K), R52.1
unnamed: D23.2 (A), R57.2
unnamed: D24.2 (A), R58.2
unnamed: D25.2 (A), R59.2
unnamed: D26.2 (A), R60.2
unnamed: D27.2 (A), U10.1
unnamed: C31.1, D27.1 (K), R61.1
unnamed: D28.2 (A), U10.3
unnamed: C32.1, D28.1 (K), R62.1
unnamed: D29.2 (A), U10.5
unnamed: C33.1, D29.1 (K), R63.1
unnamed: D30.2 (A), U10.7
unnamed: C34.1, D30.1 (K), R64.1
unnamed: D31.2 (A), R69.2
unnamed: D32.2 (A), R70.2
unnamed: D33.2 (A), R71.2
unnamed: D34.2 (A), R72.2
unnamed: D35.2 (A), U11.1
unnamed: C35.1, D35.1 (K), R73.1
unnamed: D36.2 (A), U11.3
unnamed: C36.1, D36.1 (K), R74.1
unnamed: D37.2 (A), U11.5
unnamed: C37.1, D37.1 (K), R75.1
unnamed: D38.2 (A), U11.7
unnamed: C38.1, D38.1 (K), R76.1
unnamed: D39.2 (A), R89.2
unnamed: D40.2 (A), R90.2
unnamed: D41.2 (A), R91.2
unnamed: D42.2 (A), R92.2
unnamed: D43.2 (A), R101.2
unnamed: D44.2 (A), R102.2
unnamed: D45.2 (A), R103.2
unnamed: D46.2 (A), R104.2
unnamed: D47.2 (A), R113.2
unnamed: D48.2 (A), R114.2
unnamed: D49.2 (A), R115.2
unnamed: D50.2 (A), R116.2
unnamed: D51.2 (A), R125.2
unnamed: D52.2 (A), R126.2
unnamed: D53.2 (A), R127.2
unnamed: D54.2 (A), R128.2
unnamed: J2.A5 (CC1), R131.1
unnamed: J2.B5 (CC2), R132.1
unnamed: J7.9, R16.2
unnamed: J7.12, R17.2
unnamed: J8.2, RN4.8 (R1.2), U13.4 (AIN0)
unnamed: J8.4, RN4.7 (R2.2), U13.5 (AIN1)
unnamed: C6.2, Q1.1 (G), R6.2, R7.2
unnamed: Q2.3 (C), R7.1
unnamed: Q3.2 (B1), Q3.4 (E2), U3.13 (~DTR)
unnamed: C13.1, Q3.6 (C1), R10.2, SW1.2, U4.3 (EN)
unnamed: Q3.1 (E1), Q3.5 (B2), U3.14 (~RTS)
unnamed: Q3.3 (C2), R11.2, U4.25 (IO0)
unnamed: Q4.1 (B), R85.1
unnamed: Q5.1 (B), R86.1
unnamed: Q6.1 (B), R87.1
unnamed: Q7.1 (B), R88.1
unnamed: Q8.1 (B), R97.1
unnamed: Q9.1 (B), R98.1
unnamed: Q10.1 (B), R99.1
unnamed: Q11.1 (B), R100.1
unnamed: Q12.1 (B), R109.1
unnamed: Q13.1 (B), R110.1
unnamed: Q14.1 (B), R111.1
unnamed: Q15.1 (B), R112.1
unnamed: Q16.1 (B), R121.1
unnamed: Q17.1 (B), R122.1
unnamed: Q18.1 (B), R123.1
unnamed: Q19.1 (B), R124.1
unnamed: R4.2, U2.2 (ILIM), U2.9 (ILIM)
unnamed: RN2.4 (R4.1), U5.9 (RXD2/~RMIISEL)
unnamed: RN3.2 (R2.1), U5.13 (RXER/RXD4/~PHYAD0)
unnamed: RN3.3 (R3.1), U5.8 (RXD3/~PHYAD2)
unnamed: RN3.4 (R4.1), U5.7 (RXCLK/~PHYAD1)
unnamed: H4.1, RN4.6 (R3.2), U13.7 (AIN3)
unnamed: H3.1, RN4.5 (R4.2), U13.6 (AIN2)
unnamed: C3.2, R2.2, R3.1, U1.5 (FB)
unnamed: L1.1, U1.3 (LX)
unnamed: R5.2, U2.8 (BS)
unnamed: C8.2, R8.2, R9.1, U2.5 (FB)
unnamed: U3.3 (RXD), U4.35 (TXD0/IO1)
unnamed: U3.2 (TXD), U4.34 (RXD0/IO3)
unnamed: R15.1, U4.28 (IO17)
unnamed: R26.1, U5.32 (RBIAS)
unnamed: C21.1, C22.1, U5.6 (VDDCR)
unnamed: C17.1, R24.1, U5.19 (~RST)
unnamed: R31.2, U6.18 (~RESET)
unnamed: R32.2, U7.18 (~RESET)

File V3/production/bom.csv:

Designator,Footprint,Quantity,Value,LCSC Part #
"C1, C11, C16, C17, C9",0603,5,10uF/10V,C19702
C10,CP_Elec_8x10.5,1,470uF/16V,C96179
"C12, C15, C18, C19, C20, C4, C40, C41, C42",0402,9,100nF/50V,C307331
"C13, C21, C39",0402,3,1uF/25V,C52923
C14,1206,1,1nF/2kV,C161353
C2,CP_Elec_6.3x5.4,1,47uF/35V,C129415
C22,0402,1,470pF/50V,C1537
"C23, C24, C25, C26, C27, C28, C29, C30, C31, C32, C33, C34, C35, C36, C37, C38",0805,16,33nF/50V,C1739
C3,0402,1,22pF/50V,C1555
"C5, C6",1206,2,22uF/10V,C5672
C7,0805,1,100nF/100V,C28233
C8,0603,1,12pF/50V,C38523
D1,D_SOD-123,1,SM4007PL,C64898
"D10, D15, D16, D17, D18, D2, D23, D24, D25, D26, D31, D32, D33, D34, D39, D40, D41, D42, D43, D44, D45, D46, D47, D48, D49, D50, D51, D52, D53, D54, D7, D8, D9",0603,33,EMERALD/0603,C2984266
"D11, D12, D13, D14, D19, D20, D21, D22, D27, D28, D29, D30, D35, D36, D37, D38",D_SOD-123,16,9V1/500mW,C19077407
"D3, D5",D_SMA,2,SS34,C8678
D4,D_SMA,1,SS510,C65010
D6,SOT-23-5,1,ESDS314DBV,C1847859
F1,1206,1,33V/500mA,C70077
J1,TerminalBlock_Dibo_DB142V-5.08-2P_1x02_P5.08mm_Vertical,1,VIN,C2898699
J2,USB_C_Receptacle_GCT_USB4105-xx-A_16P_TopMnt_Horizontal,1,USB_C_Receptacle_USB2.0,C2765186
"J3, J4, J5, J6",TerminalBlock_Dibo_DB141V-2.54-8P_1x08_P2.54mm_Vertical,4,DB141V-2.54-8P,C2898750
J7,RJ45_HanRun_HR911105A,1,ETHERNET,C12074
J8,TerminalBlock_Dibo_DB141V-2.54-4P_1x04_P2.54mm_Vertical,1,NTC,C2898746
L1,L_3x3mm_h1.5mm,1,"2,2uH 1,5A",C370424
L2,L_12x12mm_h6mm,1,"33uH 2,1A",C169386
L3,0805,1,2A 600R,C139168
Q1,SOT-23,1,WPM2015-3/TR,C558305
"Q10, Q11, Q12, Q13, Q14, Q15, Q16, Q17, Q18, Q19, Q4, Q5, Q6, Q7, Q8, Q9",SOT-23-Narrow,16,MMBT2222A,C8512
Q2,SOT-23,1,MMUN2211LT3G,C150229
Q3,SOT-363_SC-70-6,1,UMH3N,C62892
R1,0603,1,560R/100mW,C23204
"R10, R105, R106, R107, R108, R11, R117, R118, R119, R12, R120, R24, R6, R81, R82, R83, R84, R93, R94, R95, R96",0402,21,"10k/62,5mW",C60490
"R100, R109, R110, R111, R112, R121, R122, R123, R124, R31, R32, R7, R85, R86, R87, R88, R97, R98, R99",0402,19,"1k/62,5mW",C11702
"R101, R102, R103, R104, R113, R114, R115, R116, R125, R126, R127, R128, R33, R34, R35, R36, R45, R46, R47, R48, R57, R58, R59, R60, R69, R70, R71, R72, R89, R90, R91, R92",0603,32,"6,8k/100mW",C23212
"R129, R13, R130, R14, R41, R42, R43, R44, R53, R54, R55, R56, R65, R66, R67, R68, R77, R78, R79, R80",0402,20,"2k2/62,5mW",C25879
"R131, R132",0402,2,"5,1k/62,5mW",C105872
R15,0402,1,"22R/62,5mW",C25092
"R16, R17",0402,2,"330R/62,5mW",C25104
R2,0805,1,100k/125mW,C149504
R26,0402,1,"12,1k/62,5mW",C25852
R3,0805,1,"22,1k/125mW",C17552
"R37, R38, R39, R40, R49, R50, R51, R52, R61, R62, R63, R64, R73, R74, R75, R76",0805,16,1k8/125mW,C17398
R4,1206,1,30mR/333mW,C473665
R5,0603,1,"5,1R/100mW",C25197
R8,0603,1,300k/100mW,C23024
R9,0603,1,"52,3k/100mW",C185323
RN1,R_Array_Convex_4x0402,1,"4x49,9R/62,5mW",C136850
"RN2, RN3",R_Array_Convex_4x0402,2,"4x2,2k/62,5mW",C728724
RN4,R_Array_Convex_4x0402,1,"4x3k/62,5mW",C728735
SW1,SW_SPST_Xunpu_TS1088AR02016,1,RESET,C720477
U1,SOT-23-5_Shorter_Pins,1,SY8089A1AAC,C479074
"U10, U11, U8, U9",SOP-16_4.4x10.4mm_P1.27mm,4,OR-3H7-4,C2838427
U12,DFN-6-3x3mm_P1mm,1,AHT20,C2757850
U13,TSSOP-10_3x3mm_P0.5mm,1,ADS1115IDGS,C37593
U2,SOIC-8-1EP_3.9x4.9mm_P1.27mm_EP2.41x3.81mm_ThermalVias,1,TX4138,C329267
U3,SOIC-16_3.9x9.9mm_P1.27mm,1,CH340C,C84681
U4,ESP32-WROOM-32U,1,ESP32-WROOM-32UE-N16,C701346
U5,QFN-32-1EP_5x5mm_P0.5mm_EP3.3x3.3mm_ThermalVias,1,LAN8710A,C46185
"U6, U7",SSOP-28_5.3x10.2mm_P0.65mm,2,MCP23017_SS,C558584
